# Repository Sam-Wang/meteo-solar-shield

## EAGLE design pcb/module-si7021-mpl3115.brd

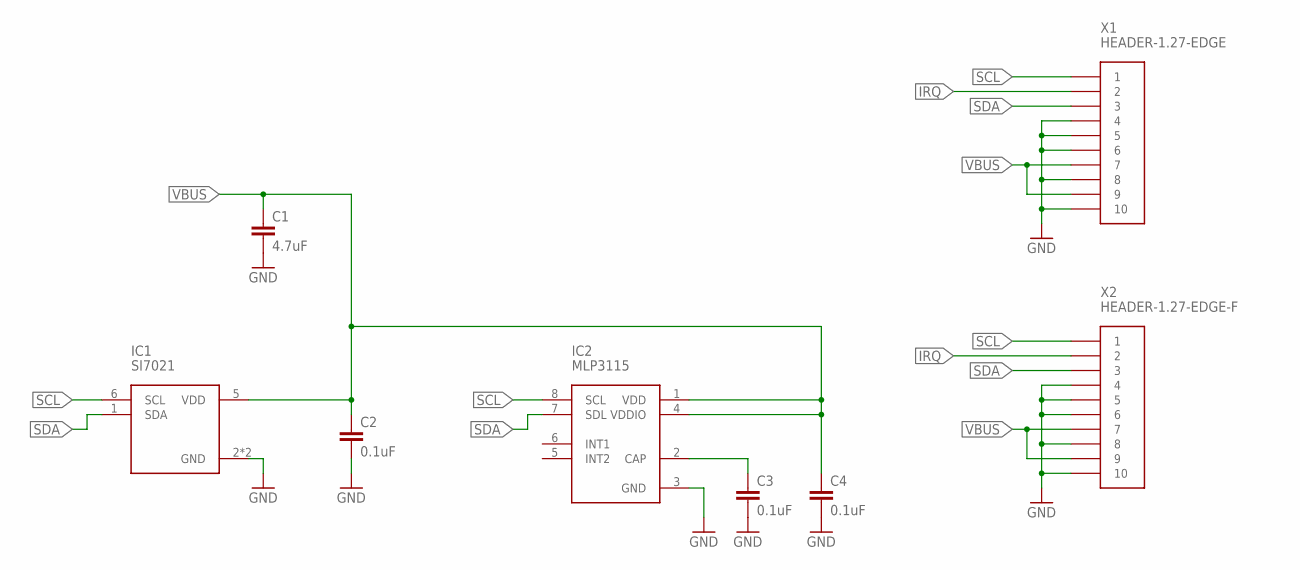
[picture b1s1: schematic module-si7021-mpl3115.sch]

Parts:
C1: 4.7uF; C0805
C2, C3, C4: 0.1uF; C0603
IC1: SI7021; DFN6-3X3
IC2: MLP3115; LGA8-3X3X1.25
X1: HEADER-1.27-EDGE
X2: HEADER-1.27-EDGE-F

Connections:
GND: C1.2, C2.2, C3.2, C4.2, IC1.2 (GND), IC1.PAD (GND), IC2.3 (GND), X1.4, X1.5, X1.6, X1.8, X1.10, X2.4, X2.5, X2.6, X2.8, X2.10
IRQ: X1.2, X2.2
unnamed: C3.1, IC2.2 (CAP)
SCL: IC1.6 (SCL), IC2.8 (SCL), X1.1, X2.1
SDA: IC1.1 (SDA), IC2.7 (SDL), X1.3, X2.3
VBUS: C1.1, C2.1, C4.1, IC1.5 (VDD), IC2.1 (VDD), IC2.4 (VDDIO), X1.7, X1.9, X2.7, X2.9

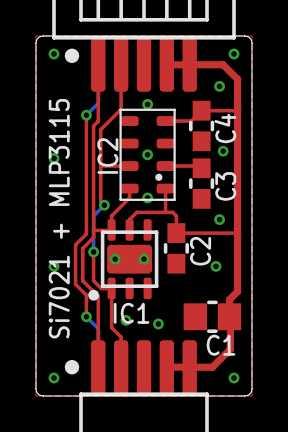
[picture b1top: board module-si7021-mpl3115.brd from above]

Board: 2 copper layers, 12.0 x 20.0 mm, 8 parts (0 on the bottom side), 6 nets.

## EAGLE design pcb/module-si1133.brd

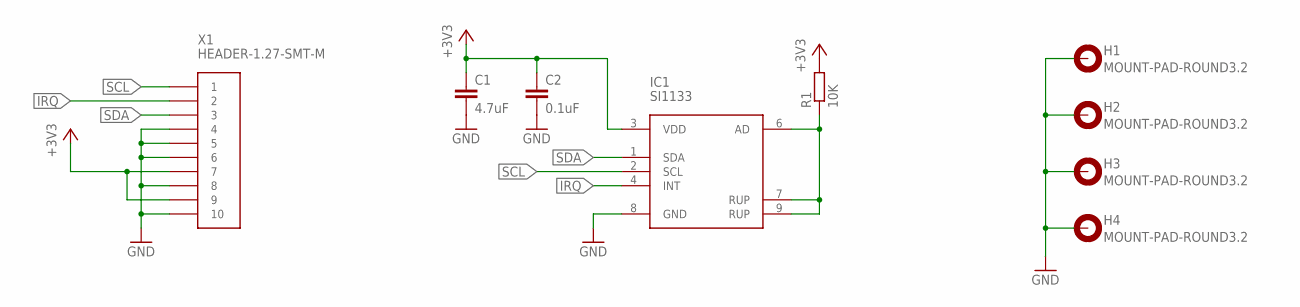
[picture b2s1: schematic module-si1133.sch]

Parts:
C1: 4.7uF; C0805
C2: 0.1uF; C0603
H1, H2, H3, H4: MOUNT-PAD-ROUND3.2; 3,2-PAD
IC1: SI1133; DFN10-2X2
R1: 10K; R0603
X1: HEADER-1.27-SMT-M

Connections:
+3V3: C1.1, C2.1, IC1.3 (VDD), R1.2, X1.7, X1.9
GND: C1.2, C2.2, H1.B3,2, H2.B3,2, H3.B3,2, H4.B3,2, IC1.8 (GND), X1.4, X1.5, X1.6, X1.8, X1.10
IRQ: IC1.4 (INT), X1.2
unnamed: IC1.6 (AD), IC1.7 (RUP), IC1.9 (RUP), R1.1
SCL: IC1.2 (SCL), X1.1
SDA: IC1.1 (SDA), X1.3

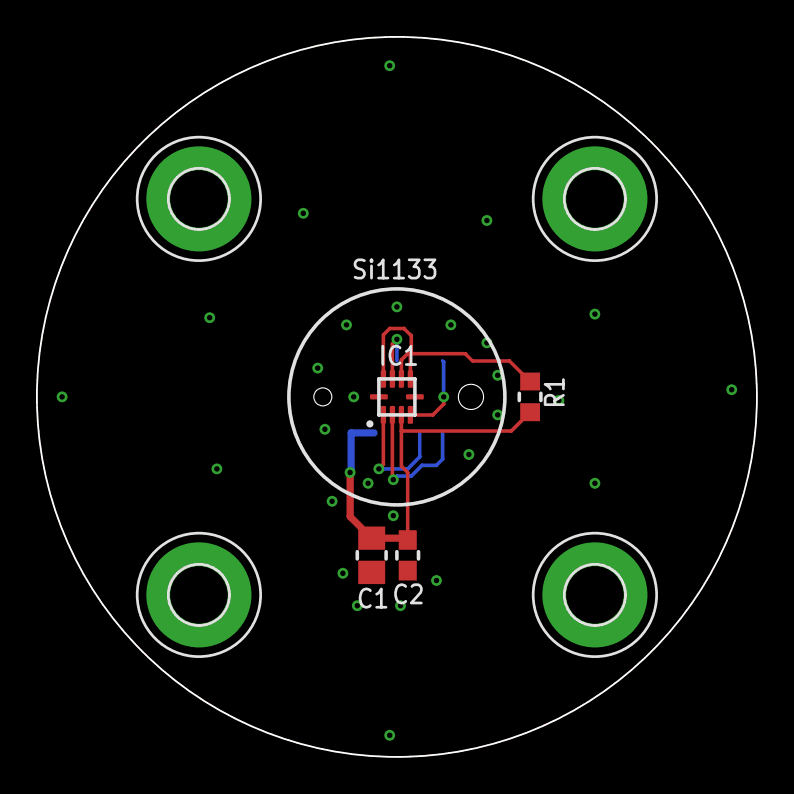
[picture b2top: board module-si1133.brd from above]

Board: 2 copper layers, 40.0 x 40.0 mm, 9 parts (1 on the bottom side), 6 nets.

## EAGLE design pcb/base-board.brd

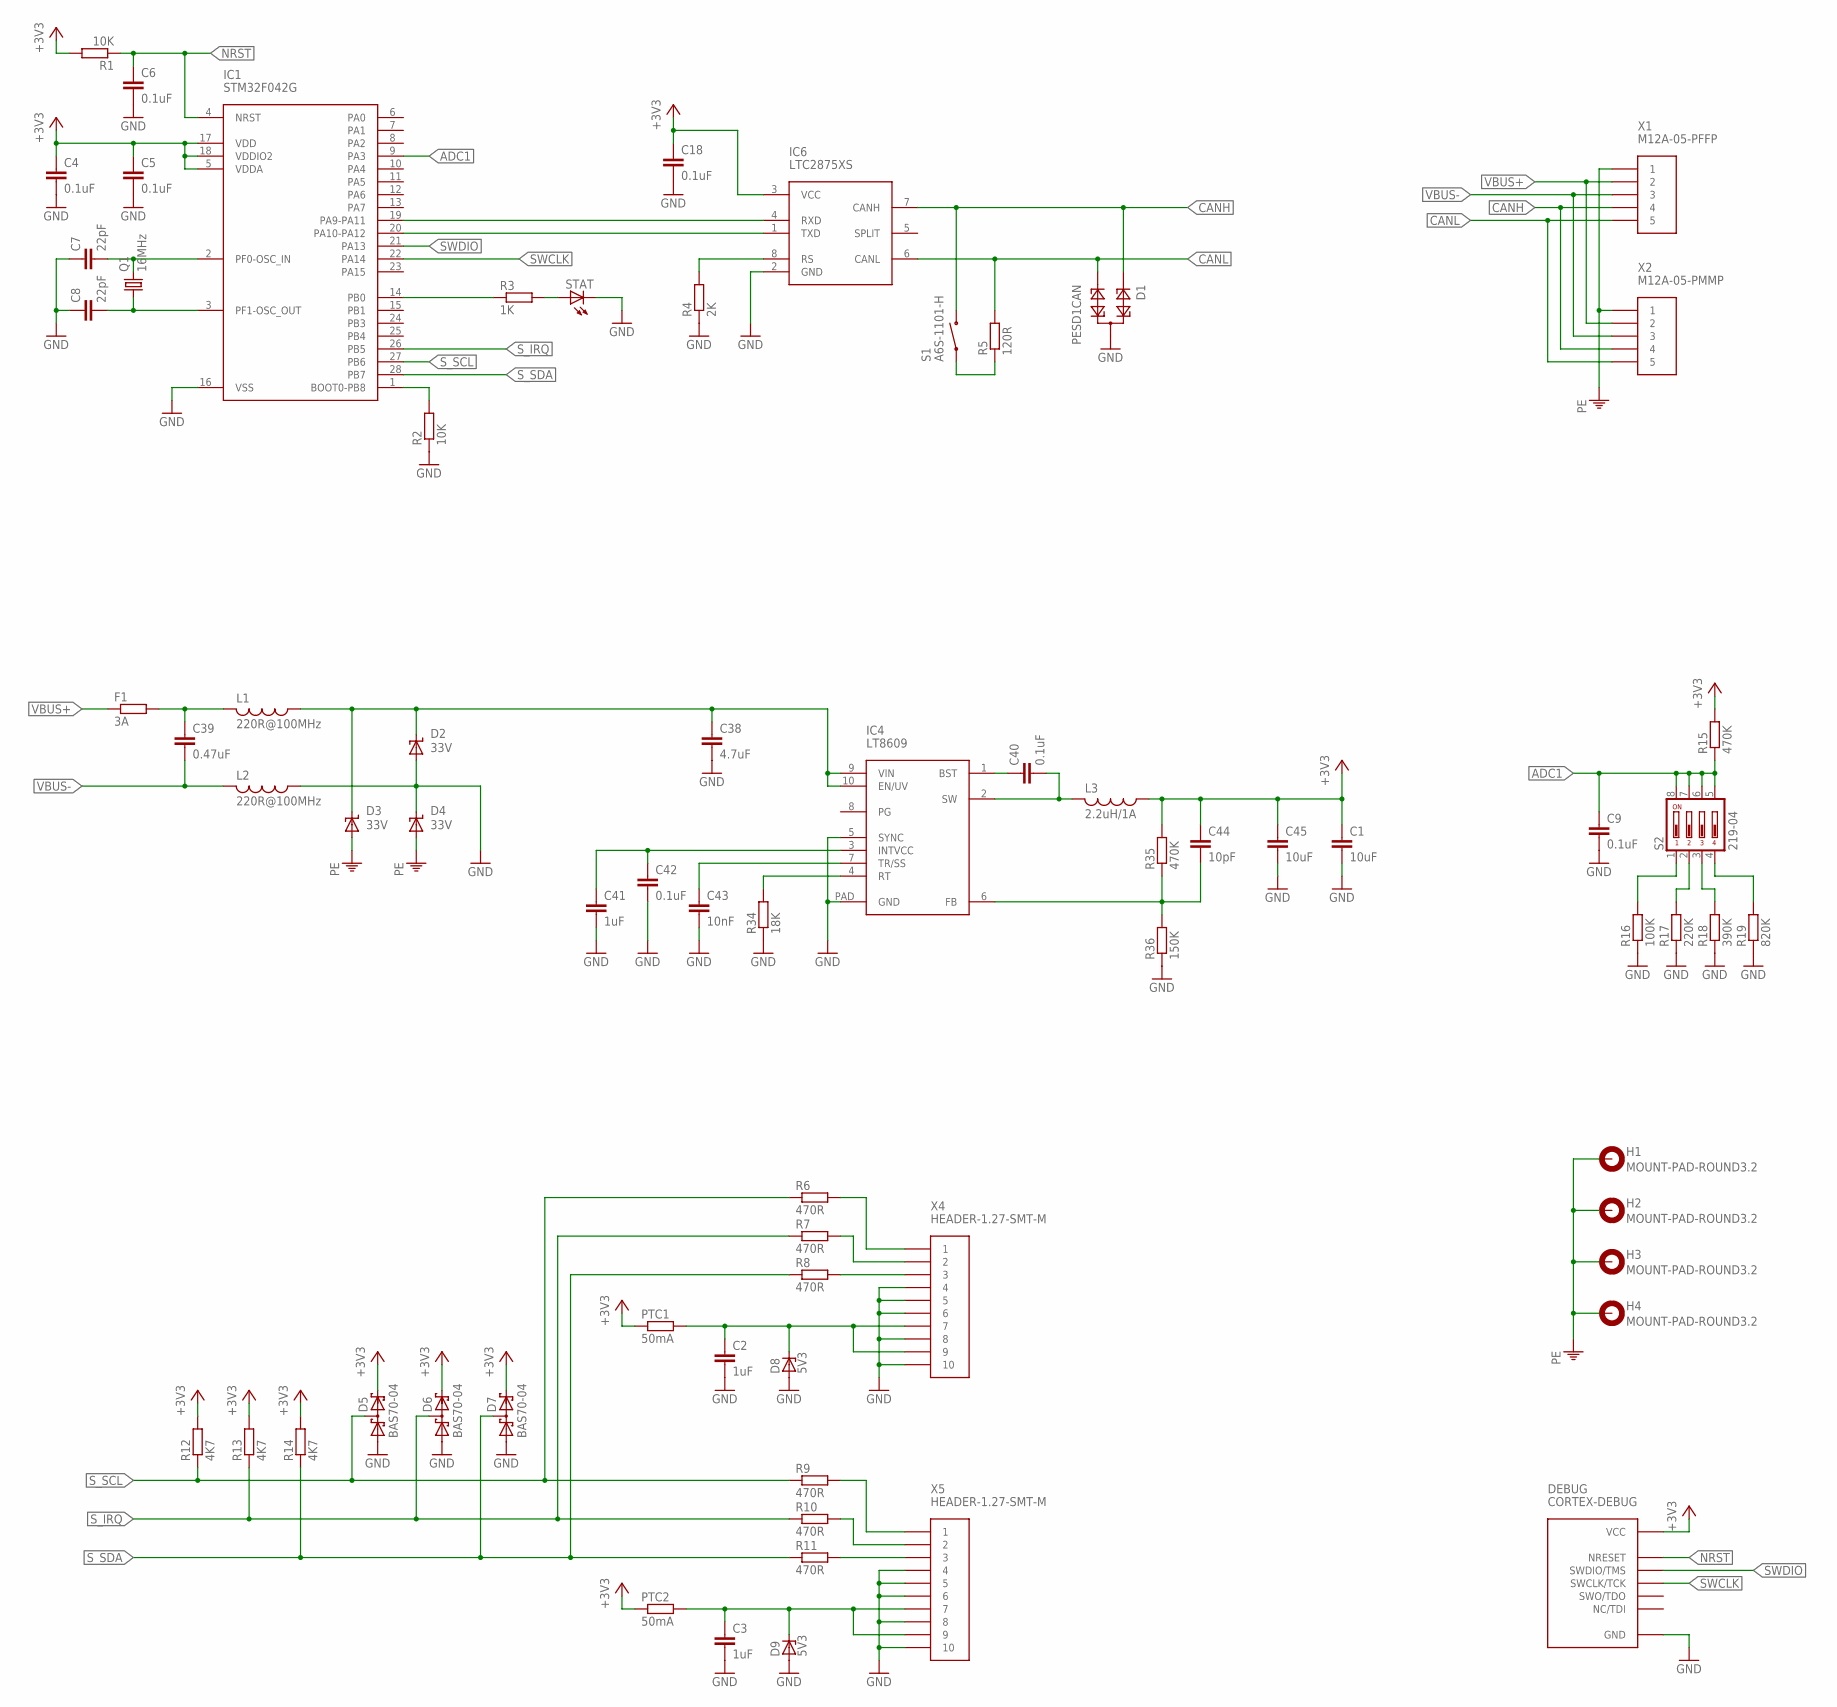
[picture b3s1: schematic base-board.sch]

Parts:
C1, C45: 10uF; C1206
C2, C3, C41: 1uF; C0603
C4, C5, C6, C9, C18, C40, C42: 0.1uF; C0603
C7, C8: 22pF; C0603
C38: 4.7uF; C1206
C39: 0.47uF; C1206
C43: 10nF; C0603
C44: 10pF; C0603
D1: PESD1CAN; SOT23
D2, D3, D4: 33V; SMBJ
D5, D6, D7: BAS70-04; SOT23
D8, D9: 5V3; SOT23
DEBUG: CORTEX-DEBUG
F1: 3A; R0805
H1, H2, H3, H4: MOUNT-PAD-ROUND3.2; 3,2-PAD
IC1: STM32F042G; UFQFPN28
IC4: LT8609; MSOP10-PAD
IC6: LTC2875XS; SOIC8
L1, L2: 220R@100MHz; L3216C
L3: 2.2uH/1A; L3216C
PTC1, PTC2: 50mA; R1206
Q1: 16MHz; XTAL_3225
R1, R2: 10K; R0603
R3: 1K; R0603
R4: 2K; R0603
R5: 120R; R0603
R6, R7, R8, R9, R10, R11: 470R; R0603
R12, R13, R14: 4K7; R0603
R15, R35: 470K; R0603
R16: 100K; R0603
R17: 220K; R0603
R18: 390K; R0603
R19: 820K; R0603
R34: 18K; R0603
R36: 150K; R0603
S1: A6S-1101-H; A6S-1
S2: 219-04; CTS-219-04
STAT: LEDCHIPLED_0805; CHIPLED_0805
X1: M12A-05-PFFP; AMP-M12A-05-PFFP
X2: M12A-05-PMMP; AMP-M12A-05-PMMP
X4, X5: HEADER-1.27-SMT-M

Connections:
+3V3: C1.1, C4.1, C5.1, C18.1, C44.1, C45.1, D5.2 (C2), D6.2 (C2), D7.2 (C2), DEBUG.VCC, IC1.5 (VDDA), IC1.17 (VDD), IC1.18 (VDDIO2), IC6.3 (VCC), L3.1, PTC1.1, PTC2.1, R1.2, R12.2, R13.2, R14.2, R15.2, R35.2
ADC1: C9.1, IC1.9 (PA3), R15.1, S2.5, S2.6, S2.7, S2.8
CANH: D1.1, IC6.7 (CANH), S1.1B (B), X1.4, X2.4
CANL: D1.2, IC6.6 (CANL), R5.2, X1.5, X2.5
GND: C1.2, C2.2, C3.2, C4.2, C5.2, C6.2, C7.1, C8.1, C9.2, C18.2, C38.2, C41.2, C42.2, C43.2, C45.2, D1.3, D2.A, D4.C, D5.1 (A1), D6.1 (A1), D7.1 (A1), D8.1 (A), D9.1 (A), DEBUG.GND1 (GND), DEBUG.GND2 (GND), DEBUG.GND_DETECT (GND), IC1.16 (VSS), IC4.5 (SYNC), IC4.PAD (GND), IC6.2 (GND), L2.1, R2.1, R4.1, R16.1, R17.1, R18.1, R19.1, R34.1, R36.1, STAT.C, X4.4, X4.5, X4.6, X4.8, X4.10, X5.4, X5.5, X5.6, X5.8, X5.10
LED: IC1.14 (PB0), R3.1
unnamed: C38.1, D2.C, D3.C, IC4.9 (VIN), IC4.10 (EN/UV), L1.1
unnamed: R3.2, STAT.A
unnamed: IC1.20 (PA10-PA12), IC6.1 (TXD)
unnamed: IC1.19 (PA9-PA11), IC6.4 (RXD)
unnamed: IC6.8 (RS), R4.2
unnamed: R5.1, S1.1A (A)
unnamed: R8.2, X4.3
unnamed: C39.1, F1.2, L1.2
unnamed: C7.2, IC1.2 (PF0-OSC_IN), Q1.3 (2)
unnamed: C8.2, IC1.3 (PF1-OSC_OUT), Q1.1
unnamed: IC1.1 (BOOT0-PB8), R2.2
unnamed: R7.2, X4.2
unnamed: C2.1, D8.3 (C), PTC1.2, X4.7, X4.9
unnamed: C3.1, D9.3 (C), PTC2.2, X5.7, X5.9
unnamed: R6.2, X4.1
unnamed: R11.2, X5.3
unnamed: R10.2, X5.2
unnamed: R9.2, X5.1
unnamed: R16.2, S2.1
unnamed: R17.2, S2.2
unnamed: R18.2, S2.3
unnamed: R19.2, S2.4
unnamed: C40.1, IC4.1 (BST)
unnamed: C40.2, IC4.2 (SW), L3.2
unnamed: C41.1, C42.1, IC4.3 (INTVCC)
unnamed: C43.1, IC4.7 (TR/SS)
unnamed: IC4.4 (RT), R34.2
unnamed: C44.2, IC4.6 (FB), R35.1, R36.2
NRST: C6.1, DEBUG.NRESET, IC1.4 (NRST), R1.1
PE: D3.A, D4.A, H1.B3,2, H2.B3,2, H3.B3,2, H4.B3,2, X1.1, X2.1
SWCLK: DEBUG.SWCLK/TCK, IC1.22 (PA14)
SWDIO: DEBUG.SWDIO/TMS, IC1.21 (PA13)
S_IRQ: D6.3 (C1A2), IC1.26 (PB5), R7.1, R10.1, R13.1
S_SCL: D5.3 (C1A2), IC1.27 (PB6), R6.1, R9.1, R12.1
S_SDA: D7.3 (C1A2), IC1.28 (PB7), R8.1, R11.1, R14.1
VBUS+: F1.1, X1.2, X2.2
VBUS-: C39.2, L2.2, X1.3, X2.3

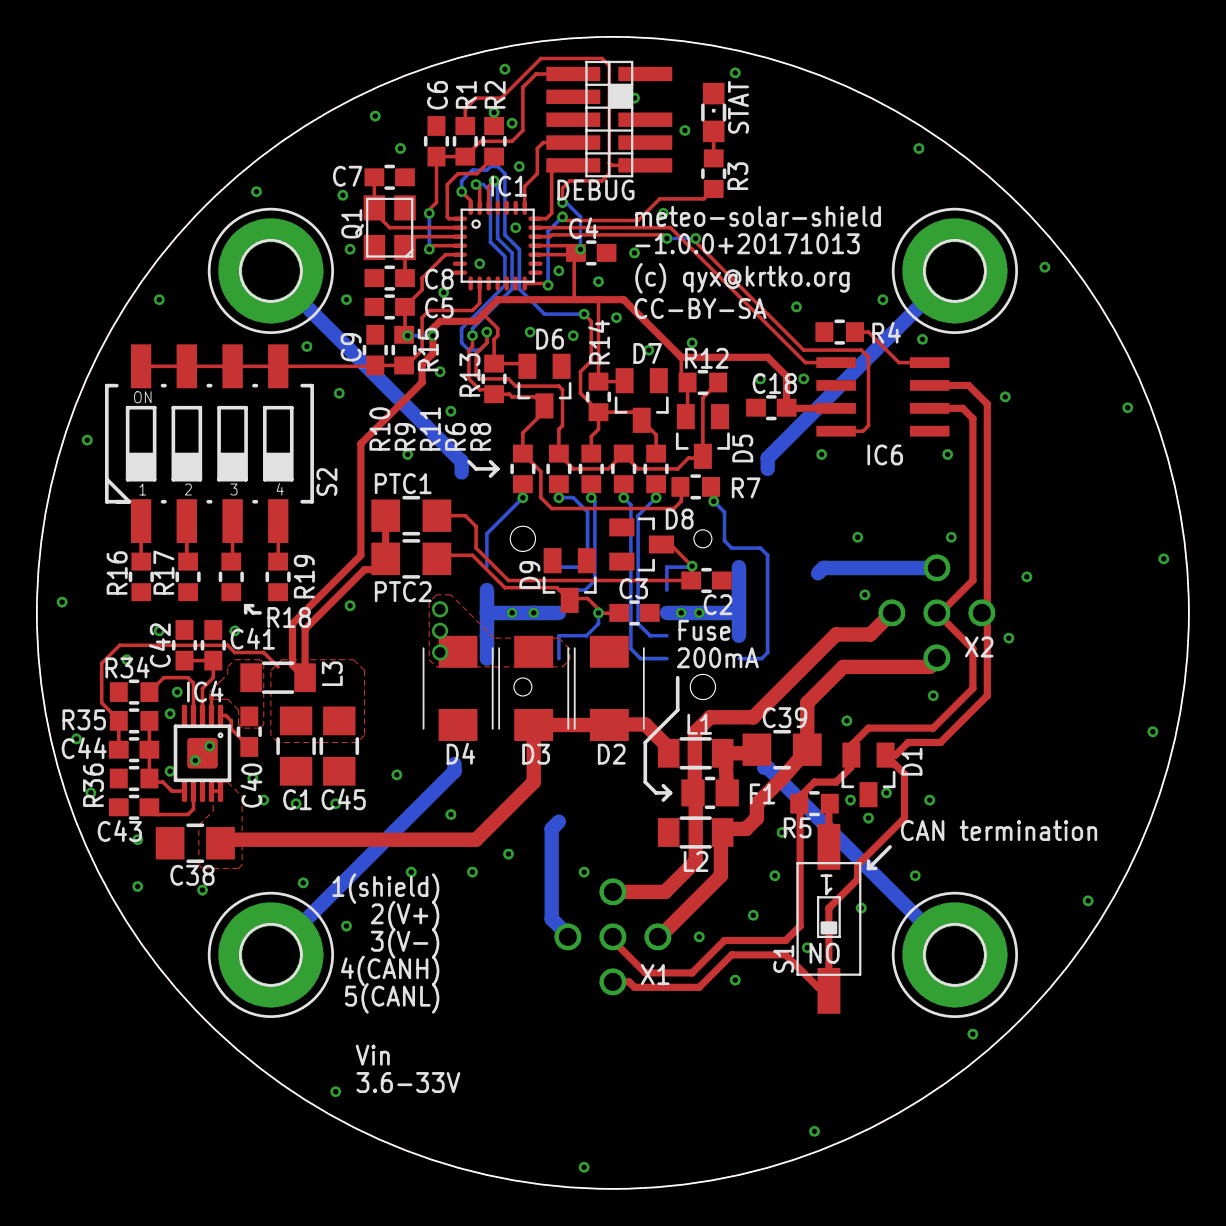
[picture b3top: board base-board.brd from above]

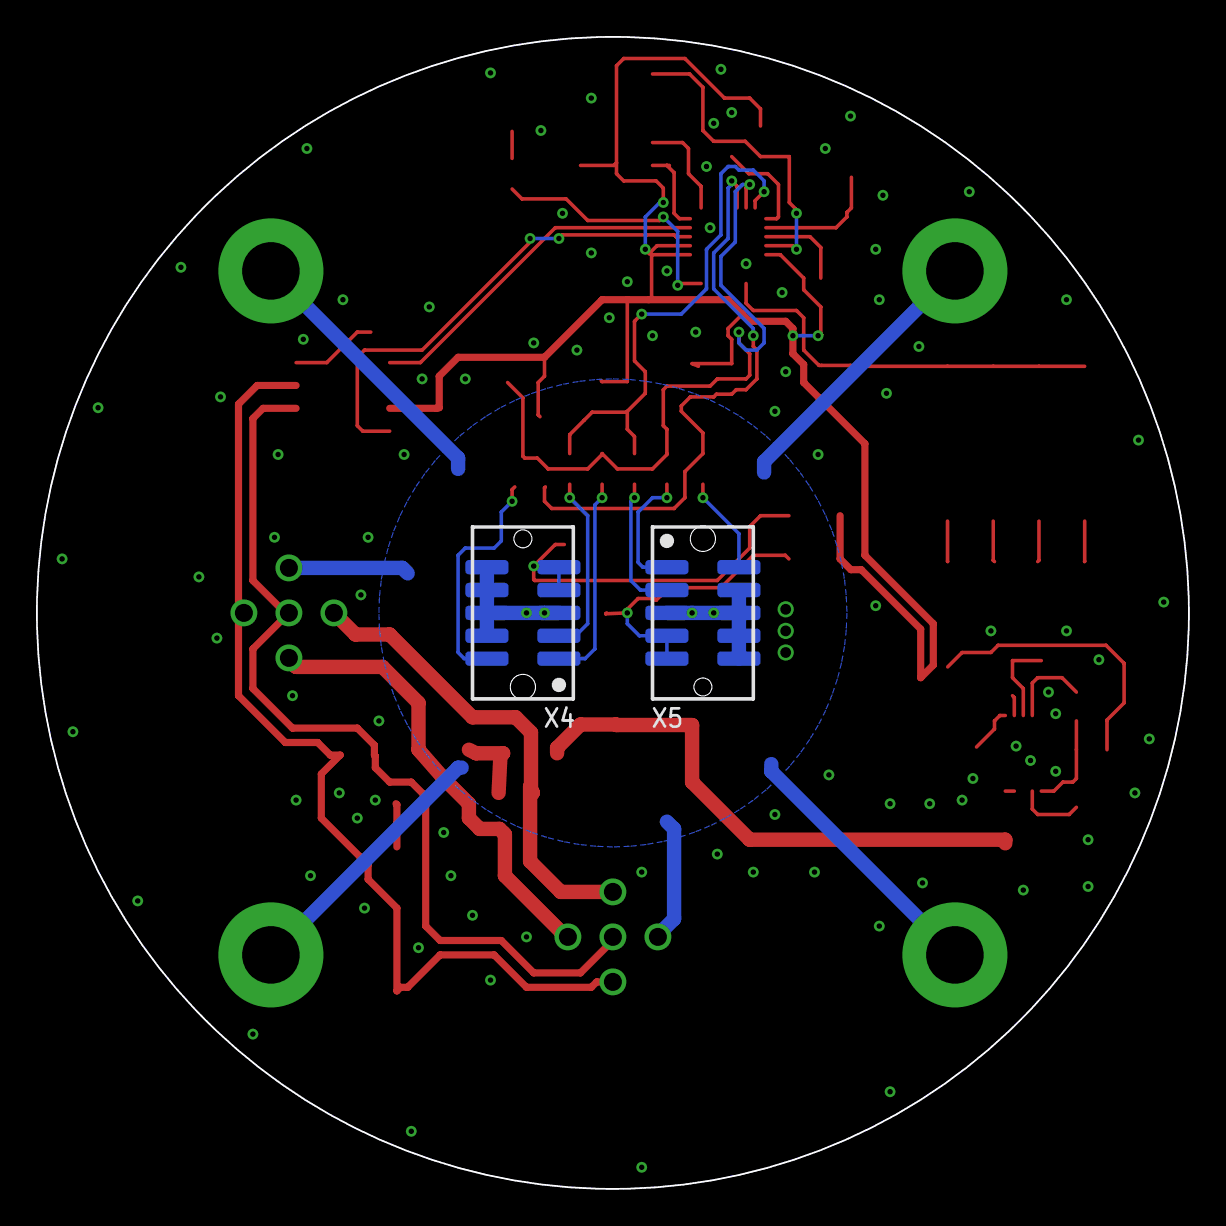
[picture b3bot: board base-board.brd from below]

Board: 2 copper layers, 64.0 x 64.0 mm, 71 parts (2 on the bottom side), 43 nets.

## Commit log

2017-11-06 Initialize the repository
2017-11-06 Add a PoC code to measure and print sensor values using semihosting
2017-11-06 Add base board schematic and layout
2017-11-06 Add a Si1133 sensor board
2017-11-06 Add a module containing Si7021 and MPL3115A2 sensors
2017-11-06 Add Gerber outputs (seeedstudio compatible)
2017-11-24 Add CAN support and refactor the code

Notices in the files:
pcb/base-board.brd:
CC-BY-SA
